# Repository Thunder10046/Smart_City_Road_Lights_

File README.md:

A smart city's road lighting system that reduces electricity wastage by adapting light intensity based on sunlight and vehicle presence.

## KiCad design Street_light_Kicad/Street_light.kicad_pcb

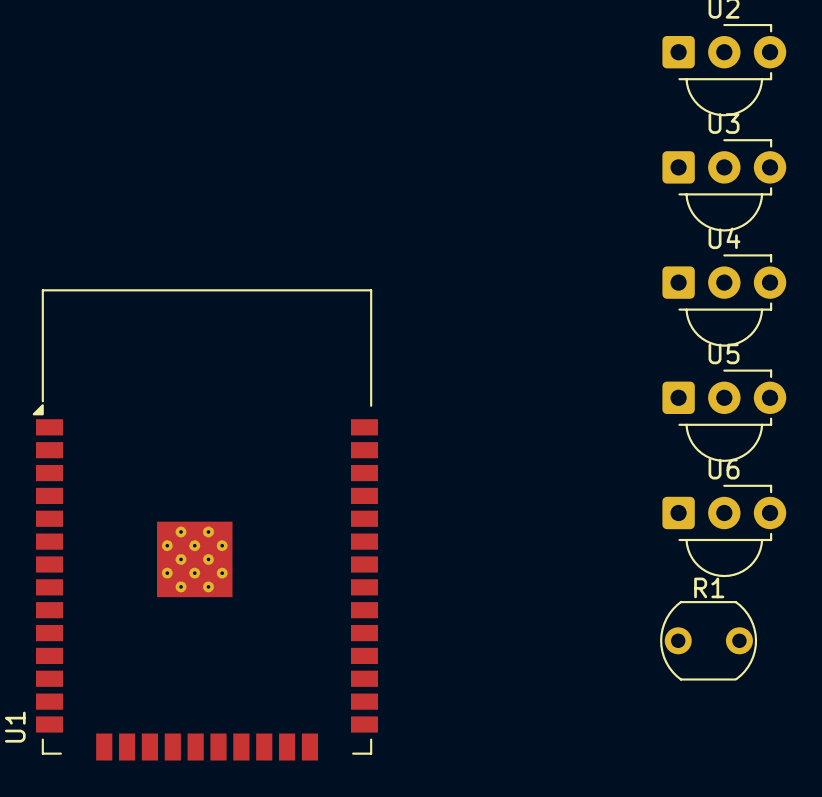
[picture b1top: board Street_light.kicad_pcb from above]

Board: 2 copper layers, 7 parts (0 on the bottom side), 8 nets, no tracks yet.

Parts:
R1: LDR07; R_LDR_5.1x4.3mm_P3.4mm_Vertical
U1: ESP32-WROOM-32
U2, U3, U4, U5, U6: TSSP58038; Vishay_MINICAST-3Pin

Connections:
+5V: R1.1, U1.29 (IO5), U2.1 (OUT), U2.3 (Vs), U3.3 (Vs), U4.3 (Vs), U5.3 (Vs), U6.3 (Vs)
GND: U2.2 (GND), U3.2 (GND), U4.2 (GND), U5.2 (GND), U6.2 (GND)
unnamed: U1.1 (GND), U1.15 (GND), U1.38 (GND), U1.39 (GND)
unnamed: U1.26 (IO4), U5.1 (OUT)
unnamed: U1.27 (IO16), U4.1 (OUT)
unnamed: U1.28 (IO17), U3.1 (OUT)
unnamed: U1.12 (IO27), U6.1 (OUT)
unnamed: R1.2, U1.6 (IO34)

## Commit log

2025-04-15 Added project source files
